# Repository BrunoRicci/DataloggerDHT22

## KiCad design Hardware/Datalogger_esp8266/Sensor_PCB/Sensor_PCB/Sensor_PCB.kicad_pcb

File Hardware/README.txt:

Hardware files.
Schematics, simulations, measurements, PCB layouts and mechanical diagrams.

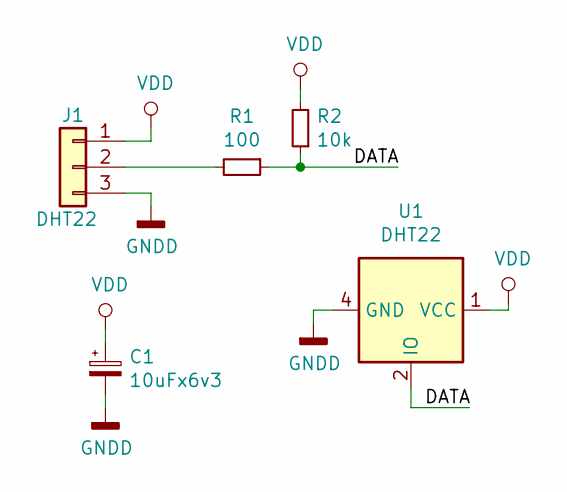
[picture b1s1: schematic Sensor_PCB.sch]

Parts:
C1: 10uFx6v3; CP_Radial_D4.0mm_P2.00mm
J1: DHT22; Molex_KK-6410-03_03x2.54mm_Straight
R1: 100; R_0805
R2: 10k; R_0805
U1: DHT22; Pin_Header_Straight_1x04_Pitch2.54mm

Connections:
/DATA: R1.1, R2.1, U1.2 (IO)
GNDD: C1.2, J1.3, U1.4 (GND)
unnamed: J1.2, R1.2
VDD: C1.1, J1.1, R2.2, U1.1 (VCC)

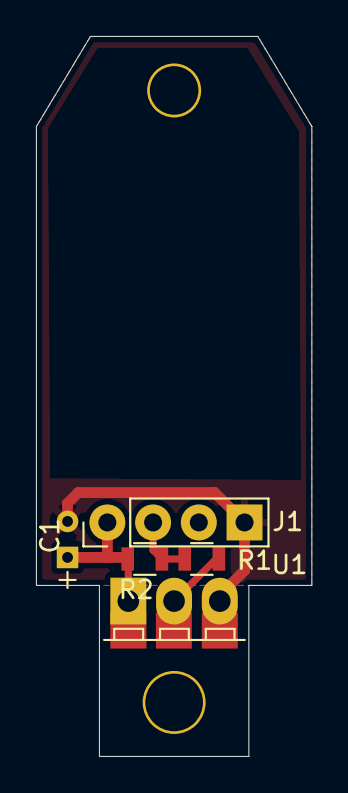
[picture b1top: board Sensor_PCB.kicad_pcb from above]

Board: 2 copper layers, 15.3 x 40.0 mm, 6 parts (0 on the bottom side), 4 nets.

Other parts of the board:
e: e; MountingHole_3.2mm_M3_DIN965_Pad

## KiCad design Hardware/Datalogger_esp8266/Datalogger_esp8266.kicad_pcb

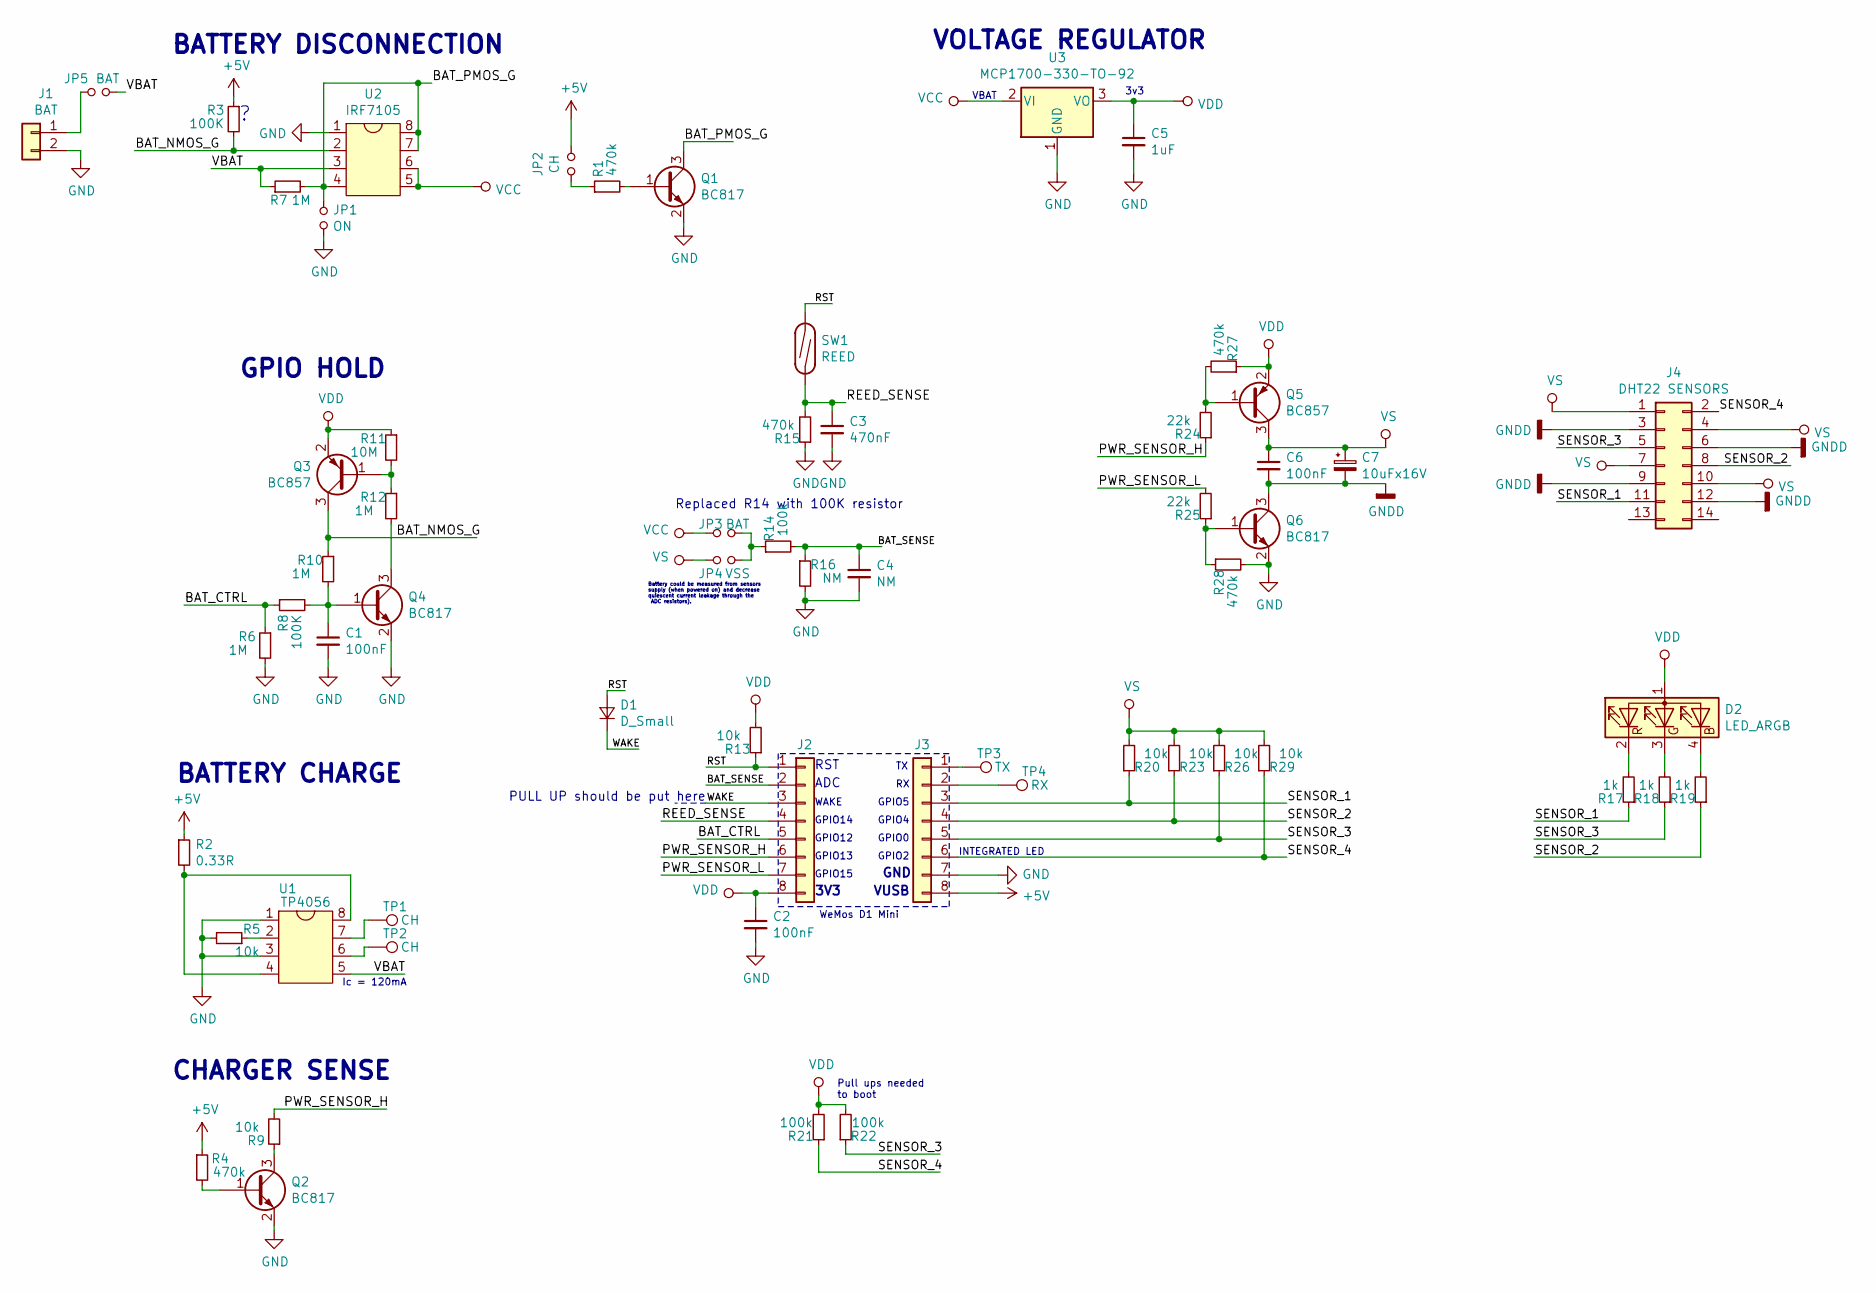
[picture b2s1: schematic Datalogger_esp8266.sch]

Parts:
C1, C2, C6: 100nF; C_0805
C3: 470nF; C_0805
C4: NM; C_0805
C5: 1uF; C_0805
C7: 10uFx16V; CP_Radial_D4.0mm_P2.00mm
D1: D_Small; D_MiniMELF
D2: LED_ARGB; LED_RGB_1210
J1: BAT; Pin_Header_Straight_1x02_Pitch2.54mm
J2, J3: Conn_01x08; Pin_Header_Straight_1x08_Pitch2.54mm
J4: DHT22 SENSORS; Multicomp_MC9A12-1434_2x07x2.54mm_Straight
JP1: ON; Solder_bridge
JP2: CH; Solder_bridge
JP3, JP5: BAT; Solder_bridge
JP4: VSS; Solder_bridge
Q1, Q2, Q4, Q6: BC817; SOT-23
Q3, Q5: BC857; SOT-23
R1, R4, R15, R27, R28: 470k; R_0805
R2: 0.33R; R_1206
R3, R8: 100K; R_0805
R5, R9, R13, R20, R23, R26, R29: 10k; R_0805
R6, R7, R10, R12: 1M; R_0805
R11: 10M; R_0805
R14, R21, R22: 100k; R_0805
R16: NM; R_0805
R17, R18, R19: 1k; R_0805
R24, R25: 22k; R_0805
SW1: REED; Pin_Header_Straight_1x02_Pitch2.00mm
TP1, TP2: CH; Solder_bridge
TP3: TX; Pin_Header_Straight_1x01_Pitch2.54mm
TP4: RX; Pin_Header_Straight_1x01_Pitch2.54mm
U1: TP4056; SOIC-8-1EP_3.9x4.9mm_Pitch1.27mm
U2: IRF7105; SOIC-8_3.9x4.9mm_Pitch1.27mm
U3: MCP1700-330-TO-92; TO-92_Inline_Wide

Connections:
/BAT_CTRL: J2.5, R6.1, R8.1
/BAT_NMOS_G: Q3.3 (C), R3.2, R10.1, U2.2
/BAT_PMOS_G: JP1.1, Q1.3 (C), R7.2, U2.4, U2.7, U2.8
/BAT_SENSE: C4.1, J2.2, R14.2, R16.1
/PWR_SENSOR_H: J2.6, R9.2, R24.1
/PWR_SENSOR_L: J2.7, R25.2
/REED_SENSE: C3.1, J2.4, R15.2, SW1.2
/RST: D1.2 (A), J2.1, R13.1, SW1.1
/SENSOR_1: J3.3, J4.11, R17.1, R20.1
/SENSOR_2: J3.4, J4.8, R19.1, R23.1
/SENSOR_3: J3.5, J4.5, R18.1, R22.1, R26.1
/SENSOR_4: J3.6, J4.2, R21.1, R29.1
/VBAT: JP5.1, R7.1, U1.5, U2.3
/WAKE: D1.1 (K), J2.3
GND: C1.2, C2.2, C3.2, C4.2, C5.2, J1.2, J3.7, JP1.2, Q1.2 (E), Q2.2 (E), Q4.2 (E), Q6.2 (E), R5.2, R6.2, R15.1, R16.2, R28.2, U1.1, U1.3, U2.1, U3.1 (GND)
GNDD: C6.2, C7.2, J4.3, J4.6, J4.9, J4.12, Q6.3 (C)
unnamed: C1.1, Q4.1 (B), R8.2, R10.2
unnamed: D2.2 (RK), R17.2
unnamed: D2.3 (GK), R18.2
unnamed: D2.4 (BK), R19.2
unnamed: J1.1, JP5.2
unnamed: J3.1, TP3.1
unnamed: J3.2, TP4.1
unnamed: JP3.1, JP4.1, R14.1
unnamed: Q1.1 (B), R1.2
unnamed: Q2.1 (B), R4.2
unnamed: Q2.3 (C), R9.1
unnamed: Q3.1 (B), R11.2, R12.1
unnamed: Q4.3 (C), R12.2
unnamed: Q5.1 (B), R24.2, R27.2
unnamed: Q6.1 (B), R25.1, R28.1
unnamed: R2.2, U1.4, U1.8
unnamed: R5.1, U1.2
unnamed: TP1.1, U1.7
unnamed: TP2.1, U1.6
VCC: JP3.2, U2.5, U2.6, U3.2 (VI)
VDD: C2.1, C5.1, D2.1 (A), J2.8, Q3.2 (E), Q5.2 (E), R11.1, R13.2, R21.2, R22.2, R27.1, U3.3 (VO)
VS: C6.1, C7.1, J4.1, J4.4, J4.7, J4.10, JP4.2, Q5.3 (C), R20.2, R23.2, R26.2, R29.2

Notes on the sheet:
RST
ADC
WAKE
GPIO14
GPIO12
GPIO13
GPIO15
GND
GPIO2
GPIO0
GPIO4
GPIO5
VUSB
3V3
3v3
VBAT
BATTERY CHARGE
BATTERY DISCONNECTION
VOLTAGE REGULATOR
GPIO HOLD
Pull ups needed to boot
INTEGRATED LED
Battery could be measured from sensors supply (when powered on) and decrease quiescent current leakage through the ADC resistors).
WeMos D1 Mini
CHARGER SENSE
Ic = 120mA
Replaced R14 with 100K resistor
PULL UP should be put here

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
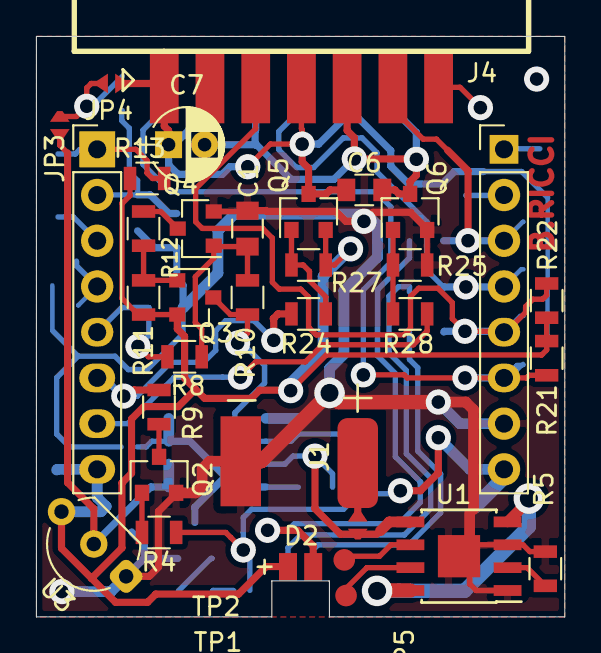
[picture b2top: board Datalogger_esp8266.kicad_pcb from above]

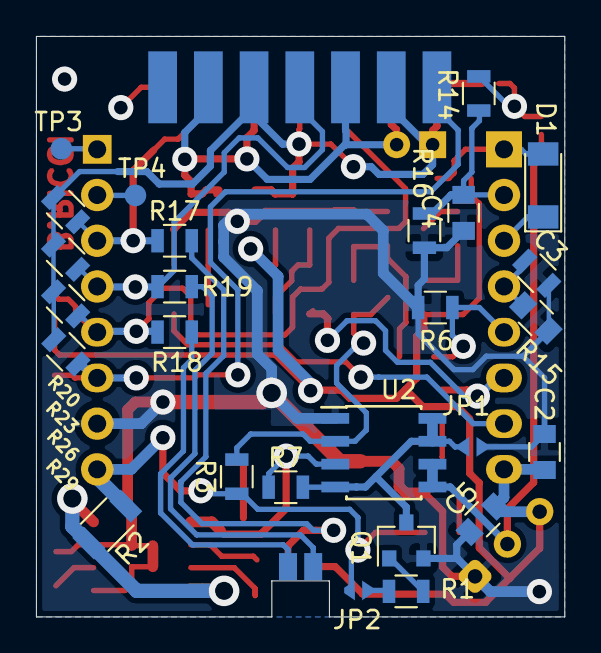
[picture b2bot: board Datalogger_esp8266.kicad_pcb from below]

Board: 2 copper layers, 29.4 x 32.2 mm, 60 parts (26 on the bottom side), 40 nets.

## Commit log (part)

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2020-03-20 Created method "setPin" in class DHT, to use a different pin with the same object methods for each sensor
2020-03-20 One DHT object per each sensor, working fine (only random bad contact in breadboard pins). Reset citcuit corrected and data gathering fine..
2020-03-21 State machines classes declared and defined (statemachine.c and statemachine.h).
2020-04-05 String handle functions created and tested. Values from measurements are being generated and formatted correctly into the POST request to the web server. To do: Function to get dictionary and generat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
2020-04-10 Web server working and RTC memory formatting working OK. Test data saved on it and pointers consistancy.
2020-04-13 test
2020-04-13 last fatal error fixed. Class RtcMemory for memory management created and tested OK.
2020-04-13 bugs fixed
2020-04-16 Testing. Functions to format and arrange data into a standard (for flash storage) in process.
2020-04-17 All read and write functions from rtc memory and flash tested and working ok.
    To do:
    - Pointers for measurements file to know where to write the next packet (not necessary now because append mode is used in the file handling).
    - Pointers for flash memory to know where to start reading "new" data (not to send repeated information).
2020-04-20 Rtc class methods created. Safe disconnect and recover data methods are pending to test. These are used to save all the variables from RTC memory to no volatile memory (flash) before power supply is 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
    Time managing functions tested. Methods for this are into RtcMemory class.
2020-04-20 Function to manage battery modified, it now works in open collector mode. Tested OK.
    Function to detect charging tested too in both firmware and hardware. Care must be taken when using it, as sensors have to be powered off.
    safeDisconnect() and recoverVariables() functions tested OK.
    RtcMemory class "var" struct members are stored together and allingned by the struct. In order to access them, writeData and readData methods must be used. The address to be read is defined into "RTC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
2020-04-22 All ready to begin to test RtcMemory::rwVariables.
2020-04-23 RtcMemory::rwVar() method tested OK. Powerdown detection tested OK.
    Test "clear" method (used when format RAM).
    Make getCurrentTimeUnix function to get time from server.
    Find the way to manage the scheduled events (measuring, transmitting, etc).
2020-04-24 bug found, read main.cpp at line 212. Commit to backup.
2020-04-24 rtc memory bug fixed.
2020-04-25 bug in statemachines.cpp fixed. State initialization flag was not being reset after setState() was called.
2020-04-27 All functions working. Method readMeasurements() should be checked because it doesn't work when called to save the data to flash.
    Packets system has base ZERO (first packet is number 0).
    To do next:
    - In STATE_FORCE_MEASUREMENT, find the way to read and write only the number of measurements stored into RTC memory and not the maximum (12).
    - Get archive packets going from "RtcMemory::var.archive_sent_pointer" to "RtcMemory::var.archive_saved_pointer - 1" and format them to be sent into the POST request.
    Fix the maximum number of measurements per request (even to use before reading from archive, to avoid reading packets that will not fit, wasting RAM) and read a maximum of that number per op
2020-04-27 RtcMemory::readMeasurements() midified: Now the "amount" argument is optional and if not specified (default value=0), the method will read all the available measurements in the RTC memory, returning 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
2020-04-27 rtcmem.readMeasurements() now used to read from RTC memory.
2020-04-27 Bug in RtcMemory::readMeasurements fixed: The formula to calculate the amount of measurements to be read (when not specified in function call) was wrong and make the program crash as it obtained amou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
2020-04-28 in process: configuration file with JSON and data transmission (connection and requests), which uses this configutation data.
2020-04-29 Configuration parameters managed to be handled without use of JSON, done with struct and a dedicated file to them, which is read, modified (if in configuration mode) and overwritten. If file won't be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
2020-04-29 function sendMeasurements() working OK. Pending: response handling and response timeout. Log events (connection times, connection error rate, battery levels, etc.)
    -Make web interface to configure parameters (config_globals) with the proper validations. Test "handleChangeConfig()" NVM saving part.
    to do: Research for methods of faster network connection (with static IP maybe), so it won't take so long to transmit the information.
2020-04-29 bug in STATE_GET_MEASUREMENTS fixed: right before changing state to transmission, it was changed again to deep_sleep, because there was no "else" sentence that changed to deep_sleep only when transmi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
2020-05-01 commit after trouble with intellisense...
2020-05-02 transmission state machine working. Check why it is taking so long (sometimes) to log into AP. Maybe cause it's the PC AP and it's not optimised or very fast. Try using the router as AP to the server.
    To do: Make code to read pending packets (also calculating all the pending ones if "packets" is not specified in functon call, as default is 0).
    CHECK: It seems that checkPowerdown is not being called properly. Better put this mechanism in RtcMemory constructor, as it has more to do with RTC memory directly than with the wake sequence itself;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
    Improve retries sequence.
2020-05-02 Battery check routine checked, working OK. Added safeDisconnect() after every transmission because archive pointers are not being saved and are lost after disconnection (frequent during development.)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
2020-05-03 data transmission machine improved. Pending packets iteration fixed.
    Check line 769 in main.cpp, condition is not the appropiate, it has a bug specified in coments.
2020-05-03 sendMeasuremends() fixed and simplified. Put timeout in connection and retries in packet sending to avoid errors.
    Changed network to the router (not the local PC AP) and it's working better.
    to do:
    - In FORCE_GET_MEASUREMENTS state, gather the amount of measurements and save them to archive (these are currently being saved when RTC memory is full). Use rwVariables().measurements_pointer to know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
    After forcing to save, send the measurements (the ones pending too).
    -test battery disconnection circuit controlled by GPIO.
2020-05-04 Force transmission fixed, now it will save all the measurements stored in memory into flash (even if it was not full) and transmit them after this. Tested OK.
    Hardware: battery disconnect circuit tested OK driven with GPIO.
    to do: Improve the packets-sent system: If any unsincronization happened, the sent_pointer will only increment with the amount of packets sent, without any reference. Trouble could appear if it's wan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
2020-05-04 Bug in STATE_FORCE_MEASUREMENT fixed:It was not saving the last measurement into archive before transmitting to the server, so it was never seen until rtc memory got filled.
2020-05-04 Get server time tested OK.
    to do:
    Fix goDeepSleep() bug, when called, the argument sent is the time minus the elapsed time (t-millis()). Inside the function, the time is all handled in microseconds.
    To fix this, send "t" argument in milliseconds (not 60e6 but 60e6, for example) and then multiply by 1000 to convert to microseconds, to send that value to the deep sleep command from SDK.
    - Data sending schedule: It is not sent when rtc memory is full anymore, data transmission must be triggered by external wake up or by the daily hour (configurable), to say, 6:00 AM.
2020-05-04 goDeepSleep function fixed.
2020-05-05 Hardware modified, now sensors are disconneted from both sides to decrease leakage current. Charge sense pin is now the same that PWR_SENSORS_PIN_P. It is pulled down when USB is connected and to det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
2020-06-24 Last firmware version + config page + other project files
2020-07-06 Changed some global_config struct members names for better understanding.
    Made AJAX for displaying current config into config mode web interface; send the modified ones via POST request.
2020-07-06 backup commit
2020-07-07 Added handle functions to modify device parameters from config mode web interface.
    Added functions to read and write the device parameters data from flash.
2020-07-13 Modified default values for config_globals.
    to do: feedback animation in buttons (when code 200 received from server) in config mode.
    - Change config mode condition to the following:
    1) force wake up with magnet.
    2) While the device is up, force a reset with the magnet and hold it for 5 seconds until the LED is YELLOW.
    3) Local AP "Datalogger" is now active and web server for config mode running.
    - Add "exit" button into config mode, which will force the device to reset and force a measurement + connection to the server.
2020-07-15 -Added auto turn off config mode when idle (no stations/client connected to AP. - Modified config mode activation sequence.
    To do: animate buttons in config mode when the device gets and execute a command (to know it's been done OK). Server should send code 200 in order to do so.
    -Add battery level into config mode.
    -Add "exit" button into config mode.
    -Add "take measurement" into config mode: shows values into page.
    -Add "test connection" into config mode: This put the device into ST+AP mode, connects to server network, and ping into the specified server IP and port. The button will turn green or red depending i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
2020-07-16 Changed some thingies in config mode visual.
2020-07-26 Last commit before devices check-out. Added 100% battery condition to enter config mode.
2020-08-06 Added function to synchronize time via serial port Added commands for entering config mode via serial. Last version uploaded to devices at 06/08/2020.
2020-08-31 Implemented daily scheduled connection. When the time of the day comes (configurable), it forces a measurement and that will lead to a connection to the server. Tested OK.
    NOTE: It will only work if device is waken up hourly (as minimum).
2020-09-02 Changed URL for sending measurements. Changed config_globals.server_ip size to 64B (for host names not being IPs).
    to do: add URL entry box in config mode.
2020-09-09 Modified config mode intarfece. Added "paths" fields (for send measurements and time synchronization) to be modifiable by the network admin.
    Added connection time field. Time of the day (UTC) when the device is connected to the network to send measurements.
    Corrected the implementation of handleChangeConfig() function in main.cpp.
    The post request values were not being correctly sent by the client (JS) and the "arg()" method wouldn't get the keys names. Now this keys can be accessed properly.
    Added 30 minutes auto turn off when in config mode.
    Modified the sendMeasurement return code condition to == 200 (it was >0, which would take 4XX return codes as successful).
    -----------------------
2020-09-09 Added license file.
2020-09-10 Modified network password field type to "password" in order to hide the value.
2020-11-16 Added configurable static IP.
    Glitch: Server won't respond when device is connected to local network with static IP.
    Maybe it could be another network parameter bug?
    Try using different gateway address
2020-11-18 Fixed packet_send_pointer bug.
    device_config.py tool tested OK.
2020-11-18 Added .gitattributes
2020-11-18 Changed .gitattributes
2020-11-18 modified .gitattributes
2020-11-30 removed "www" prefix in HTTP request. it must be placed in the config mode "host" field if necessary.
    -Automatic download batch tested OK.
    -HTTP_config input arguments tested OK.
2021-03-03 Added WPA2-Enterprise feature.
    Configuration web interface modified in order to modify the necessary parameters.
    Config_globals struct modified.
    HTML_config devices parameters database updated to support WPA2-Enterprise.
    Ready to test in prod.
